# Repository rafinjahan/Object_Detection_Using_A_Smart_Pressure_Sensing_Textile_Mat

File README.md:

# Object Detection Using a Smart Pressure-Sensing Textile Mat

This repository contains the Python code and dataset for my bachelor thesis. The project uses a 4x4 woven piezoresistive pressure mat to classify everyday kitchen objects. It uses a Random Forest machine learning model to read the pressure footprint and total weight.
I designed a custom printed circuit board using KiCad to upgrade the original breadboard prototype. This custom PCB connects the textile mat directly to the microcontroller and multiplexer for a reliable system. You can see 3D screenshots of the finished board in the images folder.

## Hardware Setup
* 4x4 piezoresistive textile mat
* Seeed Studio XIAO ESP32S3 microcontroller
* CD74HC4051E analog multiplexer

## Software Dependencies
* Python 3
* pandas
* numpy
* scikit-learn
* matplotlib
* pyserial

## Project Structure
* `code/` contains all Python scripts.
* `data/` contains CSV datasets and measurement files.
* `hardware/` contains the KiCad PCB project and Gerber manufacturing files and the 3D model of the PCB.
* `images/` contains generated PNG plots and confusion matrices.
* `thesis/` contains thesis-related files.

## Project Files
* `data/tablecloth_dataset_flattened.csv` contains the recorded dataset of physical placements.
* `code/thesis_project.py` reads serial data and saves new placements to the dataset.
* `code/live_classifier.py` trains the model and shows real time predictions on a heatmap.
* `code/confusin_matrix_result.py` calculates grouped cross validation accuracy and generates the confusion matrix.

## How It Works
The microcontroller scans the 16 sensor nodes on the fabric. Custom data acquisition software stabilizes the analog signals and filters out background noise. The system sends the pressure data to a computer for real time visualization and recording. The Python script reads this data stream and updates a visual heatmap. The system includes a noise limit of 150 ADC units. When the pressure goes above this limit the Random Forest model predicts which object is on the mat.

## Tested Objects
The dataset includes eight different classes.
* Iittala plate empty and full
* Kotikulta Ulappa bowl empty and full
* Arabia Muumi cup empty and full
* 0.33 L Coca-Cola can full
* 1.5 L Sprite bottle full

## Future Work
Future improvements could include increasing the spatial resolution of the textile sensor. Another step is deploying the trained classifier directly on the microcontroller using a TinyML framework to improve user privacy.

## Instructions

The physical setup requires connecting the textile matrix to the microcontroller and multiplexer.

1. Connect the four row pins of the 4x4 piezoresistive textile mat to the digital output pins of the microcontroller.
2. Connect the four column pins of the mat to the analog multiplexer inputs.
3. Ensure the microcontroller and multiplexer share a common ground and a stable 3.3V power supply.
4. Connect the microcontroller to the data collection computer using a USB cable.

## Microcontroller Setup (Arduino IDE)

Before running the Python scripts, you must program the microcontroller and verify it is reading the sensors correctly.

1. Install the Arduino IDE and add support for the Seeed Studio XIAO ESP32S3 board.
2. Open the provided `.ino` file in the Arduino IDE and upload it to the microcontroller.
3. Open the Serial Monitor in the Arduino IDE (set the baud rate to 115200).
4. Apply pressure to different parts of the mat. You should see a stream of numbers appearing in the Serial Monitor. If the output changes when you press the mat, the hardware is working correctly.
5. **Important:** Close the Arduino Serial Monitor before running the Python scripts, otherwise Python will not be able to connect to the serial port.

## Software Installation (Python)

The software pipeline requires Python 3 and several scientific computing libraries.

1. Install Python 3 on the data collection computer.
2. Create a virtual environment to manage the project dependencies.
3. Install the required libraries using the pip package manager.

`pip install pandas numpy scikit-learn matplotlib pyserial`

## Data Collection and Heatmap Visualization

The data collection script reads raw analog values from the serial port and visualizes the spatial pressure distribution.

1. Place the smart textile mat on a flat and rigid surface to ensure consistent pressure readings.
2. Run the data collection script from your terminal using `python data_collection.py`.
3. Observe the real time heatmap interface to verify all 16 sensor nodes respond correctly to physical pressure.
4. Place a test object on the mat and allow the sensor values to stabilize for a few seconds.
5. Press the designated keyboard key to record the current matrix values and the object label into the dataset file named `tablecloth_dataset_flattened.csv`.

## Model Training and Evaluation

The machine learning model uses the collected CSV dataset to train the Random Forest classifier.

1. Verify the dataset file contains sufficient samples for all tested object categories.
2. Run the model evaluation script from the terminal using `python model_evaluation.py`.
3. The script will automatically load the CSV dataset and format the spatial arrays into one dimensional features.
4. The Random Forest algorithm will train on the data and output the grouped cross validation accuracy results.
5. Review the generated confusion matrix image to analyze the classification performance across different objects.

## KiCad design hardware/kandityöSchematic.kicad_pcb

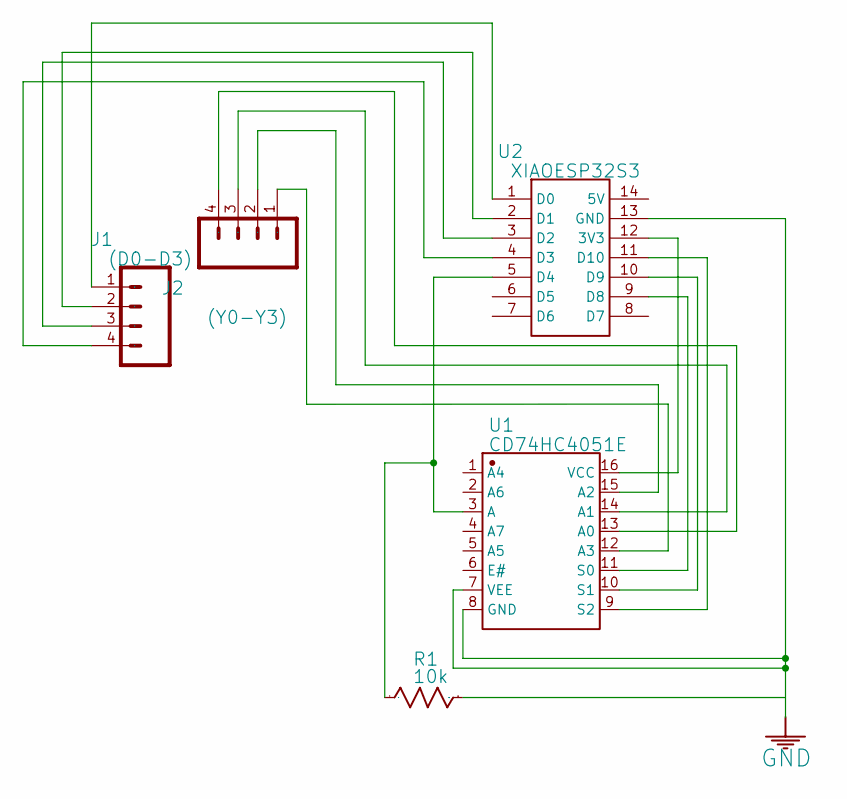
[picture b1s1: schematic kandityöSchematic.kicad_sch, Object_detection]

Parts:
J1: (D0-D3); PinHeader_1x04_P2.54mm_Vertical
J2: (Y0-Y3); PinHeader_1x04_P2.54mm_Vertical
R1: 10k; R_0805_2012Metric_Pad1.20x1.40mm_HandSolder
U1: CD74HC4051E; SOIC-16_3.9x9.9mm_P1.27mm; Manufacturer Part CD74HC4051E
U2: XIAOESP32S3; MODULE_XIAO_ESP32_S3

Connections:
GND: R1.1, U1.7 (VEE), U1.8 (GND), U2.13 (GND)
unnamed: J2.4, U1.13 (A0)
unnamed: J2.3, U1.14 (A1)
unnamed: J2.2, U1.15 (A2)
unnamed: J2.1, U1.12 (A3)
unnamed: R1.2, U1.3 (A), U2.5 (D4)
unnamed: U1.11 (S0), U2.9 (D8)
unnamed: U1.10 (S1), U2.10 (D9)
unnamed: U1.9 (S2), U2.11 (D10)
unnamed: U1.16 (VCC), U2.12 (3V3)
unnamed: J1.1, U2.1 (D0)
unnamed: J1.2, U2.2 (D1)
unnamed: J1.3, U2.3 (D2)
unnamed: J1.4, U2.4 (D3)

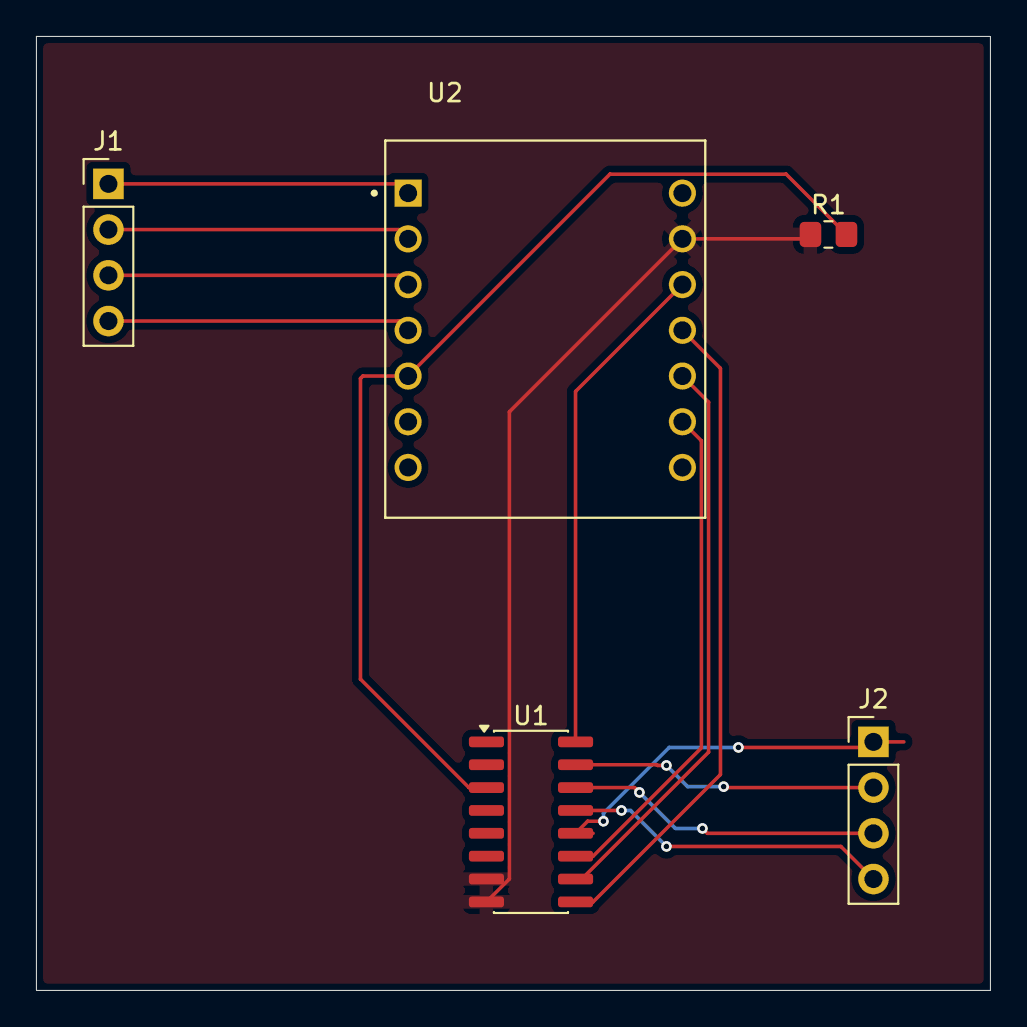
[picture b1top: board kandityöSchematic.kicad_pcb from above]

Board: 2 copper layers, 53.0 x 53.0 mm, 5 parts (0 on the bottom side), 14 nets.

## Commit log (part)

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2026-06-08 Thesis code added
    Added all of the code
2026-06-08 Add README for Smart Textile Object Detection project
    This README file provides an overview of the Smart Textile Object Detection project, including hardware setup, software dependencies, project files, and how the system works.
2026-06-08 Revise README for clarity and structure
2026-06-08 Remove citations from README for clarity
2026-06-11 Initial plan
2026-06-11 Reorganize repository into code data images thesis folders
2026-06-11 Fix relocated paths in code test script
2026-06-11 Addded thesis pdf
2026-06-27 Add Arduino code for pressure matrix reading
    Initialize multiplexer and read pressure matrix values.
2026-06-27 Rename thesis_arduino_serial to thesis_arduino_serial.ino
2026-06-27 Enhance README with setup and usage instructions
    Added detailed instructions for microcontroller setup, software installation, data collection, and model training.
